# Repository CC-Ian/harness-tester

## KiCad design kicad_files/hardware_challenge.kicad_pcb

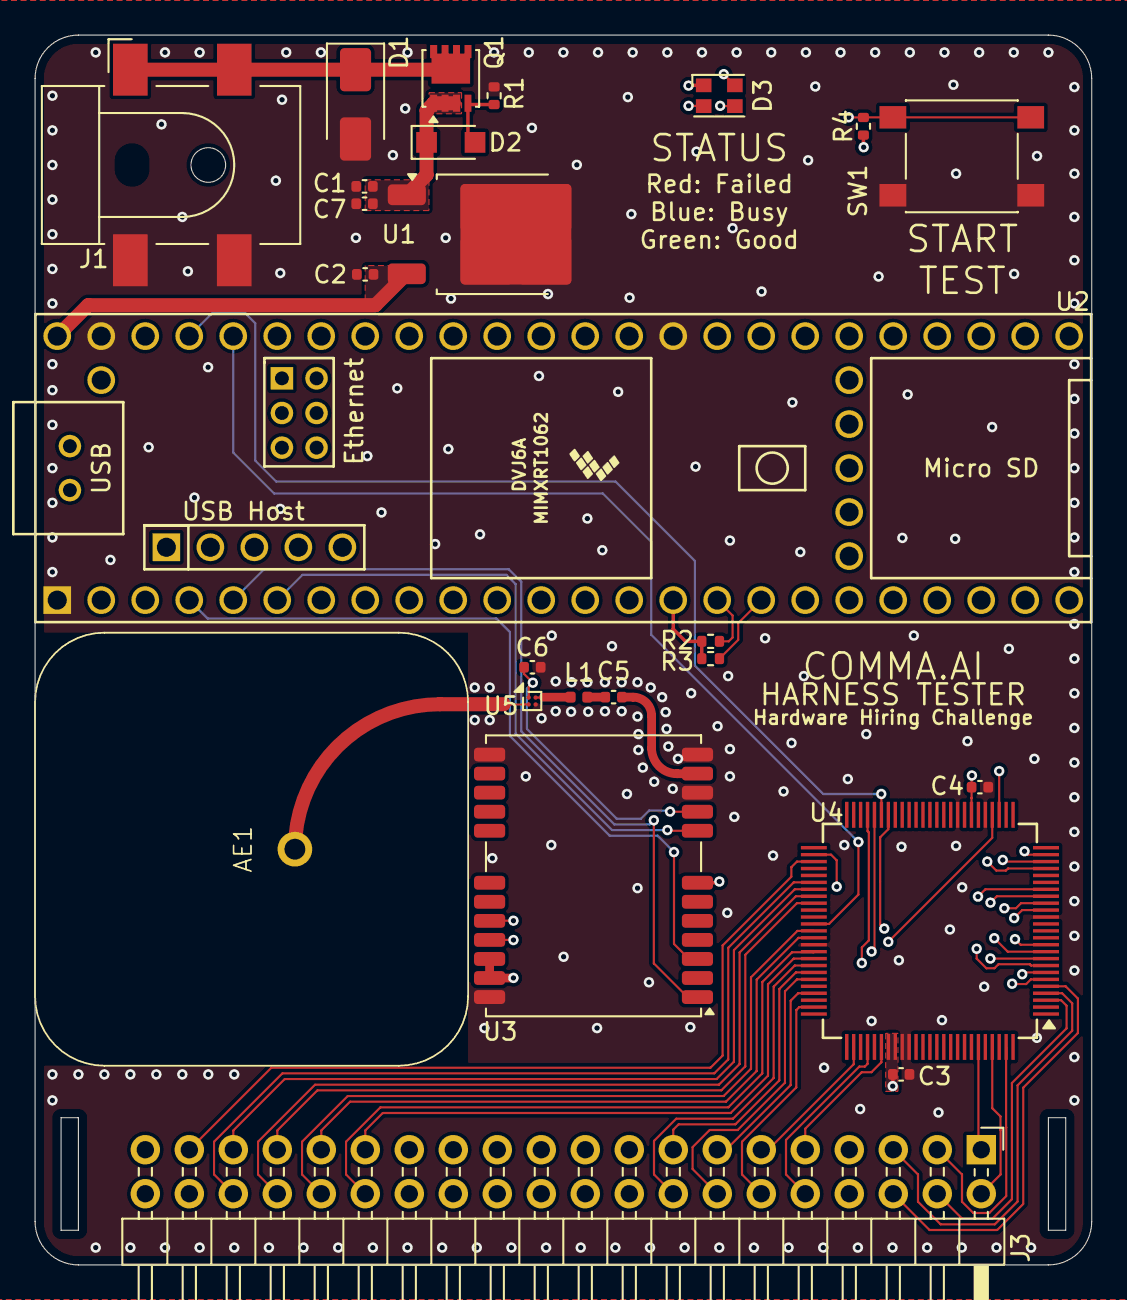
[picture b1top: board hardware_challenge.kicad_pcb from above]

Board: 4 copper layers, 61.0 x 71.0 mm, 25 parts (0 on the bottom side), 64 nets.

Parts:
AE1: ANT-GNSSCP-TH25L1
C1: 1u; C_0402_1005Metric
C2, C3, C4, C5: 100n; C_0402_1005Metric
C6: 1n; C_0402_1005Metric
C7: 10u; C_0402_1005Metric
D1: SMAJ16A; D_SMA
D2: PMEG10020ELR; Nexperia_CFP3_SOD-123W
D3: ASMB-KTF0-0A306; LED_ASMB-KTF0-0A306
J1: 12V INPUT; BarrelJack_CLIFF_FC681465S_SMT_Horizontal
J3: Cable header; PinHeader_2x20_P2.54mm_Horizontal
L1: 12n; L_0402_1005Metric
Q1: SiSS27DN; Vishay_PowerPAK_1212-8_Single
R1: 1k; R_0402_1005Metric
R2, R3: 4k7; R_0402_1005Metric
R4: 10k; R_0402_1005Metric
SW1: TEST BUTTON; SW_SPST_PTS645
U1: L7805; TO-252-2
U2: Teensy4.1; Teensy41
U3: NEO-M8N; ublox_NEO
U4: CY8C9560A-24AXIT; TQFP-100_12x12mm_P0.4mm
U5: MAX2679; WLP-4_0.83x0.83mm_P0.4mm

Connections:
+3.3V: C3.1, C4.1, D3.1 (A), R2.1, R3.1, R4.1, U2.15 (3V3), U2.46 (3V3), U3.7 (VDD_USB), U3.22 (V_BCKP), U3.23 (VCC), U4.32 (Vdd), U4.82 (Vdd), U4.83 (Vdd)
+5V: C2.1, U1.3 (OUT), U2.48 (VIN)
+12V: C1.1, C7.1, D2.1 (K), Q1.1 (S), Q1.2 (S), Q1.3 (S), U1.1 (IN)
BTN_TEST: R4.2, SW1.2, U2.10 (8_TX2_IN1)
CBL_0: J3.1, U4.95 (GPort0_Bit0_PWM7)
CBL_1: J3.2, U4.97 (GPort0_Bit1_PWM5)
CBL_2: J3.3, U4.99 (GPort0_Bit2_PWM3)
CBL_3: J3.4, U4.3 (GPort0_Bit3_PWM1)
CBL_4: J3.5, U4.4 (GPort0_Bit4_PWM7)
CBL_5: J3.6, U4.5 (GPort0_Bit5_PWM5)
CBL_6: J3.7, U4.6 (GPort0_Bit6_PWM3)
CBL_7: J3.8, U4.7 (GPort0_Bit7_PWM1)
CBL_8: J3.9, U4.81 (GPort1_Bit0_PWM6)
CBL_9: J3.10, U4.79 (GPort1_Bit1_PWM4)
CBL_10: J3.11, U4.77 (GPort1_Bit2_PWM2)
CBL_11: J3.12, U4.74 (GPort1_Bit3_PWM0)
CBL_12: J3.13, U4.72 (GPort1_Bit4_PWM6)
CBL_13: J3.14, U4.70 (GPort1_Bit5_PWM4/A6)
CBL_14: J3.15, U4.69 (GPort1_Bit6_PWM2/A5)
CBL_15: J3.16, U4.68 (GPort1_Bit7_PWM0/A4)
CBL_16: J3.17, U4.47 (GPort2_Bit0_PWM14/A3)
CBL_17: J3.18, U4.46 (GPort2_Bit1_PWM12/A2)
CBL_18: J3.19, U4.44 (GPort2_Bit2_PWM8/WD)
CBL_19: J3.20, U4.29 (GPort2_Bit3_PWM11/A1)
CBL_20: J3.21, U4.8 (GPort3_Bit0_PWM7)
CBL_21: J3.22, U4.9 (GPort3_Bit1_PWM5)
CBL_22: J3.23, U4.10 (GPort3_Bit2_PWM3)
CBL_23: J3.24, U4.11 (GPort3_Bit3_PWM1)
CBL_24: J3.25, U4.16 (GPort3_Bit4_PWM15)
CBL_25: J3.26, U4.17 (GPort3_Bit5_PWM13)
CBL_26: J3.27, U4.18 (GPort3_Bit6_PWM11)
CBL_27: J3.28, U4.19 (GPort3_Bit7_PWM9)
CBL_28: J3.29, U4.67 (GPort4_Bit0_PWM6)
CBL_29: J3.30, U4.66 (GPort4_Bit1_PWM4)
CBL_30: J3.31, U4.64 (GPort4_Bit2_PWM2)
CBL_31: J3.32, U4.63 (GPort4_Bit3_PWM0)
CBL_32: J3.33, U4.59 (GPort4_Bit4_PWM14)
CBL_33: J3.34, U4.58 (GPort4_Bit5_PWM12)
CBL_34: J3.35, U4.57 (GPort4_Bit6_PWM10)
CBL_35: J3.36, U4.56 (GPort4_Bit7_PWM8)
CBL_36: J3.37, U4.53 (GPort5_Bit0_PWM10)
CBL_37: J3.38, U4.52 (GPort5_Bit1_PWM8)
CBL_38: J3.39, U4.22 (GPort5_Bit2_PWM11)
CBL_39: J3.40, U4.23 (GPort5_Bit3_PWM9)
CY_INT: U2.45 (23_A9_CRX1_MCLK1), U4.45 (INT)
CY_RST_N: U2.44 (22_A8_CTX1), U4.62 (RESET_N)
CY_SCL: R2.2, U2.16 (24_A10_TX6_SCL2), U4.24 (SCL)
CY_SDA: R3.2, U2.17 (25_A11_RX6_SDA2), U4.28 (SDA)
GND: C1.2, C2.2, C3.2, C4.2, C6.2, C7.2, D1.2 (A2), J1.2, J1.3, R1.2, SW1.1, U1.2 (GND), U2.1 (GND), U2.34 (GND), U2.47 (GND), U3.10 (GND), U3.12 (GND), U3.13 (GND), U3.24 (GND), U4.15 (Vss), U4.30 (A0), U4.34 (Vss), U4.65 (Vss), U4.84 (Vss), U4.85 (Vss), U5.B2 (G)
LED_B: D3.2 (BK), U2.9 (7_RX2_OUT1A)
LED_G: D3.3 (GK), U2.8 (6_OUT1D)
LED_R: D3.4 (RK), U2.7 (5_IN2)
unnamed: AE1.1 (A), U5.B1
unnamed: C5.2, L1.1
unnamed: D1.1 (A1), J1.1, Q1.5 (D)
unnamed: D2.2 (A), Q1.4 (G), R1.1
unnamed: L1.2, U5.A2
unnamed: C5.1, U3.11 (RF_IN)
unnamed: C6.1, U3.9 (VCC_RF), U5.A1 (Vcc)
UBX-RST_N: U2.6 (4_BCLK2), U3.8 (~RESET)
UBX-RXD: U2.2 (0_RX1_CRX2_CS1), U3.21 (RXD/SPI_MOSI)
UBX-SAFEBOOT: U2.5 (3_LRCLK2), U3.1 (~SAFEBOOT)
UBX-TIMEPULSE: U2.4 (2_OUT2), U3.3 (TIMEPULSE)
UBX-TXD: U2.3 (1_TX1_CTX2_MISO1), U3.20 (TXD/SPI_MISO)

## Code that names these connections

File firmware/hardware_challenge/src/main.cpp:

#include <Arduino.h>
#include <SD.h>
#include "CY8C9560.h"

enum Status {FAILED, BUSY, GOOD};

#define PIN_UBX_TIMEPULSE 2
#define PIN_UBX_SAFEBOOT 3
#define PIN_UBX_RST_N 4
#define PIN_LED_R 5
#define PIN_LED_G 6
#define PIN_LED_B 7
#define PIN_BTN_TEST 8

#define DBG_SERIAL Serial
#define UBX_SERIAL Serial1
#define SD_CS BUILTIN_SDCARD

#define NUM_HARNESS_PINS 40
// Example connection matrix, just for illustration
uint64_t EXPECTED_CONNECTIONS[NUM_HARNESS_PINS] = {
  0b1000000000000000000000000010000000000000,
  0b0100001000000000000000000000000000000000,
  0b0010000000000000000000000000000000000000,
  0b0001100000001000000000000000000010000000,
  0b0000100000100000000000000001000000000000,
  0b0000010100000000000000000000000000000000,
  0b0000001000000000100000000000000000000000,
  0b0000000100000000000000000000001000001000,
  0b0000000010000000000000000000000000000000,
  0b0000000001000000000000000000000010000000,
  0b0010000000100000000000000000000000000000,
  0b0000000000010000000010000000000000000000,
  0b0000000000001000000000000000000000010000,
  0b0000000000000100000000000000000000000001,
  0b0000000000000010000000001000000000000000,
  0b0000000000001001000000000100000000000000,
  0b0000000000000000100000000000000000000000,
  0b0000010000000000010000000000000000000000,
  0b0000000000000000001000000000000000000000,
  0b0000000000000000000100000000100000000000,
  0b0000000000000000000010000000000000000000,
  0b0000000000000000000001000000000000000000,
  0b0000000000000000000000100000000000000000,
  0b0000000000000000000000010000000001000000,
  0b0000000000000000000000001000000000000000,
  0b0000000000001000000000000100000000000000,
  0b0000000000000000000000000010000000000000,
  0b0000000000100010000000001001000000001000,
  0b0000000000000000000000000000100000000000,
  0b0000000000001000000000000000010000010000,
  0b0000000000000000000000000000001000000000,
  0b0000000000000000000000000000000100000000,
  0b0000000000000000000000000000000010100000,
  0b0000000000000000000000000000000001000010,
  0b0000100000000000000000100000000000100000,
  0b0000010000000000000000000000000000011000,
  0b0000000000000000000000000000000000001000,
  0b0000000000000000000000000000010000000100,
  0b0000000000000000000000000000000000000010,
  0b0000000000000000000000000000000000000001,
};

CY8C9560 cy;
char utc_time[20], date[20];
bool time_fixed = false;

void set_status(Status s) {
  digitalWrite(PIN_LED_R, !(s == FAILED));
  digitalWrite(PIN_LED_B, !(s == BUSY));
  digitalWrite(PIN_LED_G, !(s == GOOD));
}

void process_nmea(char *buf, int len) {
  buf[len] = 0;
  if (strncmp(buf, "$GPRMC", 6) == 0) {
    if (sscanf(buf, "$GPRMC,%10[^,],%*c,%*f,%*c,%*f,%*c,%*f,%*f,%6[^,]", utc_time, date) == 2 && !time_fixed) {
      DBG_SERIAL.println("Time received. Ready to test some harnesses!");
      set_status(GOOD);
      time_fixed = true;
    } else if (!time_fixed) {
      DBG_SERIAL.println("Failed to parse $GPRMC");
    }
  }
}

void log_result(bool passed) {
  File f = SD.open("results.txt", FILE_WRITE);
  if (f) {
    f.print(date); f.print(" - "); f.print(utc_time); f.print(": "); // raw date + time strings are fine here
    f.println(passed ? "Passed" : "Failed");
    f.close();
  } else {
    DBG_SERIAL.println("Failed to open log file");
  }
}

void setup() {
  // Serial ports
  DBG_SERIAL.begin(115200);
  UBX_SERIAL.begin(9600);

  // GPIO
  set_status(BUSY);
  pinMode(PIN_BTN_TEST, INPUT);
  pinMode(PIN_UBX_TIMEPULSE, INPUT);

  // add pinMode assertions for safeboot and rst.
  pinMode(PIN_UBX_SAFEBOOT, OUTPUT);
  pinMode(PIN_UBX_RST_N, OUTPUT);
  digitalWrite(PIN_UBX_SAFEBOOT, LOW);
  digitalWrite(PIN_UBX_RST_N, HIGH);

  // Begin CY. If address is incorrect, note it and stop running.
  if (!cy.begin()) {
    DBG_SERIAL.println("Incorrect CY8C95X0");
    set_status(FAILED);
    while(1);
  }

  // SD card
  if (!SD.begin(SD_CS)) {
    DBG_SERIAL.println("SD card initialization failed");
    while (1);
  }

  DBG_SERIAL.println("Waiting for GPS time lock...");
}

char nmea_buf[64];
int nmea_idx = 0;
void loop() {
  // Process incoming ublox messages
  while (UBX_SERIAL.available()) {
    nmea_buf[nmea_idx++] = UBX_SERIAL.read();
    if (nmea_buf[nmea_idx - 1] == '\n' || nmea_buf[nmea_idx - 1] == '\r') {
      process_nmea(nmea_buf, nmea_idx);
      nmea_idx = 0;

      // Jump out the while here to make sure we're not missing any button presses under high load
      break;
    }
  }

  // Return if we don't have a time fix yet
  if (!time_fixed) return;
  set_status(GOOD);

  // Start testing only if the button is pressed
  // Move the code into this loop. Returning won't do anything.
  if (digitalRead(PIN_BTN_TEST) == LOW) {
    set_status(BUSY);

    // Test harness by checking the connectivity of every pin
    // Invert logic. Start passing, set false for every failure. This ensures a failure is properly caught.
    bool passed = true;
    for (int i = 0; i < NUM_HARNESS_PINS; i++) {
      uint64_t output_mask = 1 << i;
      cy.set_output(output_mask, output_mask);
      cy.set_pd_inputs(~output_mask);

      uint64_t values = cy.read_inputs() & ~output_mask;

      // Log connections to the serial port
      DBG_SERIAL.printf("Pin %d: ", i);
      // Readability. For me.
      for (int j = 0; j < NUM_HARNESS_PINS; j++){
        DBG_SERIAL.printf("%d", (values & (1 << j)) ? 1 : 0);
      }
      DBG_SERIAL.println();

      if (values != EXPECTED_CONNECTIONS[i]) {
        passed = false;
      }
    }
    set_status(passed ? GOOD : FAILED);

    // Show and log results
    DBG_SERIAL.println(passed ? "Harness passed!" : "Harness failed!");
    log_result(passed);

    // Add delay so the operator can actually see the LED.
    delay(1000);
    
  }
  
}

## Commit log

2024-10-04 Preliminary run thought. Nice and quick. Hitting mostly the hardware, with a hint of the software.
2024-11-08 text based solution file
